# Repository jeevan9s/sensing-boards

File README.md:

# Sensing Boards

A collection of sensor and embedded boards designed in KiCad.

## Boards

### Hall-FX Module

An ESP32-S3-based Hall-effect sensing board built around the TI TMAG5273
magnetic sensor. The design also includes USB-C, battery and power-management
circuitry, status LEDs, pushbuttons, ESD protection, and supply decoupling.
I worked with [Johann Samuel Nana](https://www.linkedin.com/in/johann-s-nana/)
([GitHub](https://github.com/sam93502)) on the schematic capture.

- [KiCad project](hall-fx/HALL_module.kicad_pro)
- [Schematic](hall-fx/HALL_module.kicad_sch)
- [PCB layout](hall-fx/HALL_module.kicad_pcb)
- Custom footprints, symbol, and 3D models are in the [hall-fx directory](hall-fx/).

### ToF Sensor Module

A time-of-flight distance-sensing board using the ST VL53L0CX sensor. Its
schematic provides a 3.3 V supply, I2C connections, and an XSHUT control signal,
with ESD protection and decoupling. Designed for Penguin, the modules are
intended to be chained using their I2C input and output connections.

- [KiCad project](tof-module/TOF_module.kicad_pro)
- [Schematic](tof-module/TOF_module.kicad_sch)
- [PCB layout](tof-module/TOF_module.kicad_pcb)

## Working with the designs

Open each board's `.kicad_pro` file in KiCad to view or edit the project. Check
the corresponding schematic for connector pin assignments and electrical
requirements before connecting a board. The project directories also contain
`.zip` archives of the PCB files.

---
Jeevan Sanchez, 2026

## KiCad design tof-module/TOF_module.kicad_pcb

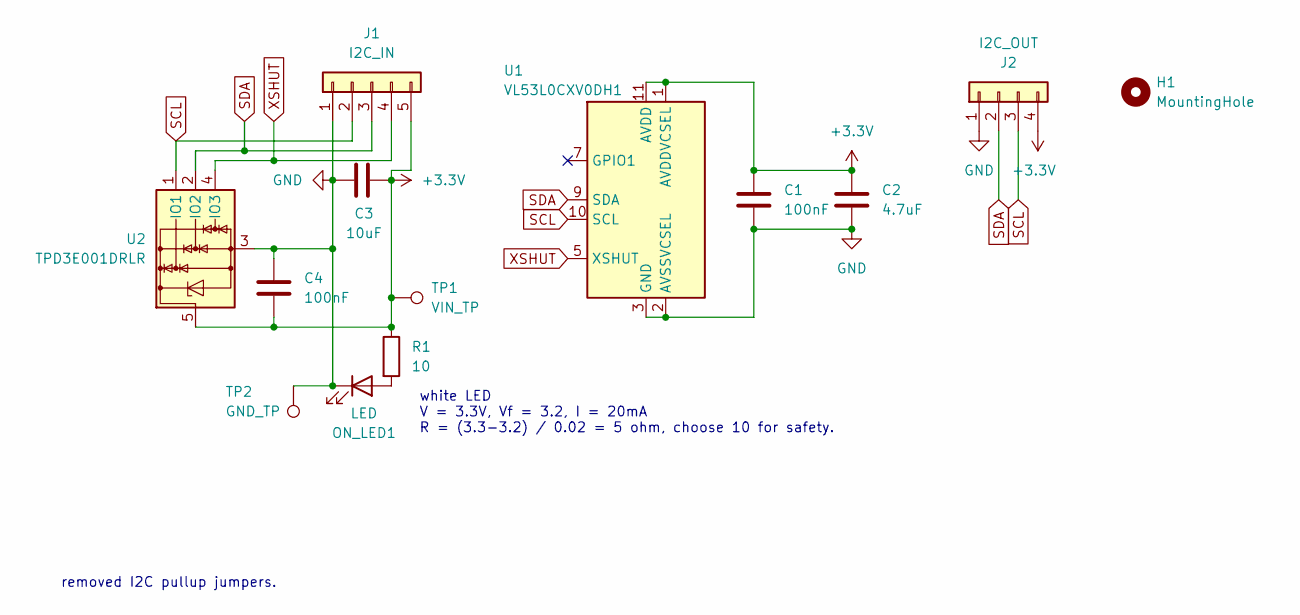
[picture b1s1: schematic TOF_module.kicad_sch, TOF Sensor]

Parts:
C1, C4: 100nF; C_0603_1608Metric
C2: 4.7uF; C_0603_1608Metric
C3: 10uF; C_0805_2012Metric
H1: MountingHole; MountingHole_2.1mm
J1: I2C_IN; JST_GH_BM05B-GHS-TBT_1x05-1MP_P1.25mm_Vertical
J2: I2C_OUT; JST_GH_SM04B-GHS-TB_1x04-1MP_P1.25mm_Horizontal
ON_LED1: LED; LED_0603_1608Metric
R1: 10; R_0603_1608Metric
TP1: VIN_TP; TestPoint_Pad_1.0x1.0mm
TP2: GND_TP; TestPoint_Pad_1.0x1.0mm
U1: VL53L0CXV0DH1; ST_VL53L1x
U2: TPD3E001DRLR; SOT-553

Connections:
+3.3V: C1.1, C2.1, C3.2, C4.1, J1.5, J2.4, R1.1, TP1.1 (1_1), U1.1 (AVDDVCSEL), U1.11 (AVDD), U2.5
GND: C1.2, C2.2, C3.1, C4.2, J1.1, J1.MP, J2.1, J2.MP, ON_LED1.1 (K), TP2.1 (1_1), U1.2 (AVSSVCSEL), U1.3 (GND), U1.4 (GND), U1.6 (GND), U1.12 (GND), U2.3
unnamed: ON_LED1.2 (A), R1.2
SCL: J1.2, J2.3, U1.10 (SCL), U2.1 (IO1)
SDA: J1.3, J2.2, U1.9 (SDA), U2.2 (IO2)
XSHUT: J1.4, U1.5 (XSHUT), U2.4 (IO3)

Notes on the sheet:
removed I2C pullup jumpers.
white LED V = 3.3V, Vf = 3.2, I = 20mA R = (3.3-3.2) / 0.02 = 5 ohm, choose 10 for safety.

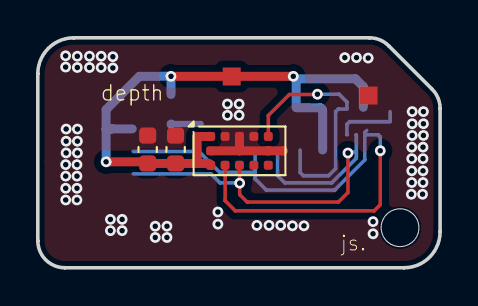
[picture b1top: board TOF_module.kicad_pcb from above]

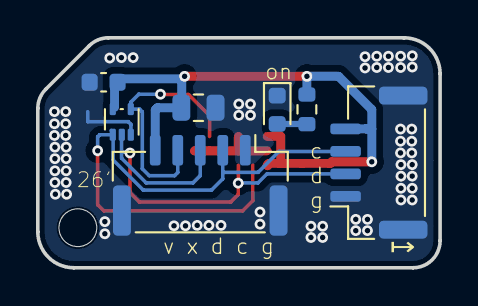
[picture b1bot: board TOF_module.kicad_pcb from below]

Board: 2 copper layers, 22.3 x 12.8 mm, 13 parts (7 on the bottom side), 6 nets.

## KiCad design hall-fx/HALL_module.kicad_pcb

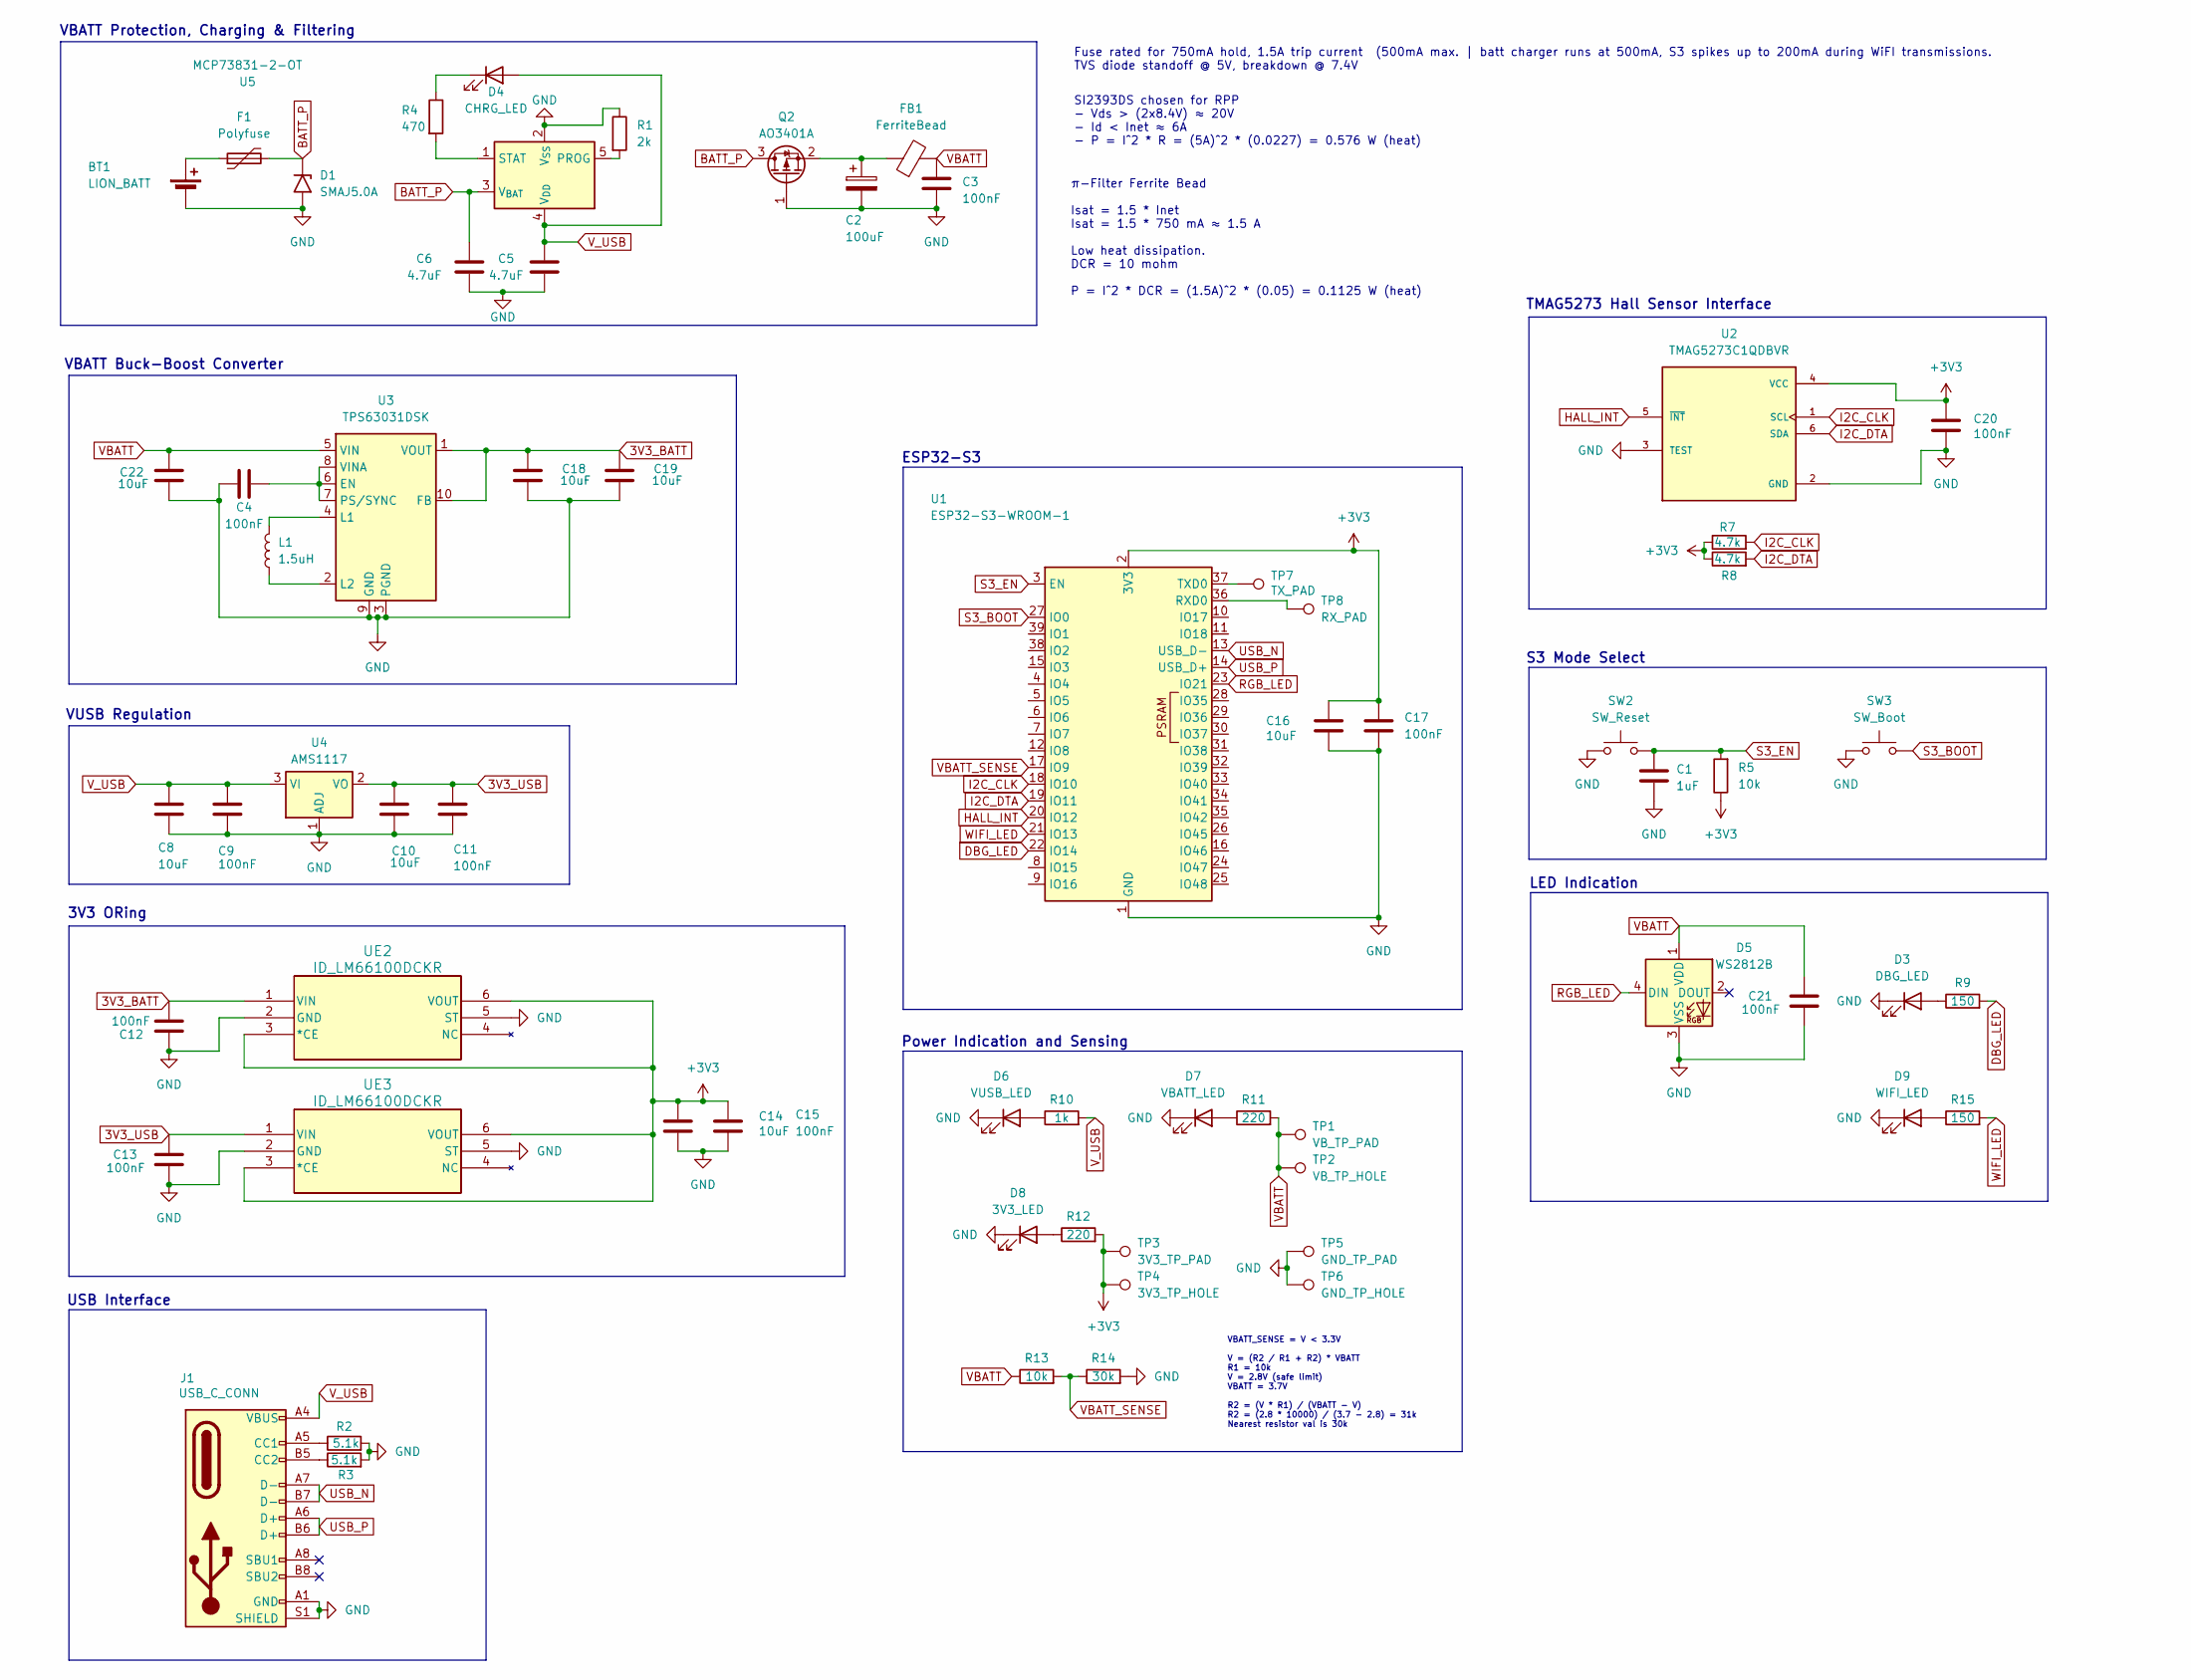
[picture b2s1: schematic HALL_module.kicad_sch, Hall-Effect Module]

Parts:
BT1: LION_BATT; JST_PH_B2B-PH-K_1x02_P2.00mm_Vertical
C1: 1uF; C_0402_1005Metric
C2: 100uF; CP_Elec_6.3x7.7; Digikey 10-EEE-FTH101XALCT-ND
C3: 100nF; C_0603_1608Metric
C4, C9, C11, C12, C13, C15, C17, C20, C21: 100nF; C_0402_1005Metric
C5, C6: 4.7uF; C_0603_1608Metric
C8, C10, C14, C16, C18, C19, C22: 10uF; C_0805_2012Metric
D1: SMAJ5.0A; D_SMF; Digikey SMAJ5.0ALFCT-ND
D3: DBG_LED; LED_0603_1608Metric
D4: CHRG_LED; LED_0603_1608Metric
D5: WS2812B; LED_WS2812B_PLCC4_5.0x5.0mm_P3.2mm
D6: VUSB_LED; LED_0603_1608Metric
D7: VBATT_LED; LED_0603_1608Metric
D8: 3V3_LED; LED_0603_1608Metric
D9: WIFI_LED; LED_0603_1608Metric
F1: Polyfuse; Fuse_1206_3216Metric_Pad1.42x1.75mm_HandSolder; Digikey NANOSMDC075F-2CT-ND
FB1: FerriteBead; R_0805_2012Metric
J1: USB_C_CONN; USB_C_Receptacle_G-Switch_GT-USB-7010ASV; LCSC C5178541
L1: 1.5uH; L_1210_3225Metric_Pad1.42x2.65mm_HandSolder; Digikey 490-5335-1-ND
Q2: AO3401A; SOT-23
R1: 2k; R_0402_1005Metric
R2, R3: 5.1k; R_0402_1005Metric
R4: 470; R_0402_1005Metric
R5, R13: 10k; R_0402_1005Metric
R7, R8: 4.7k; R_0402_1005Metric
R9, R15: 150; R_0402_1005Metric
R10: 1k; R_0402_1005Metric
R11, R12: 220; R_0402_1005Metric
R14: 30k; R_0402_1005Metric
SW2: SW_Reset; SW_5-B-B-B-A_XKB; LCSC C561514
SW3: SW_Boot; SW_5-B-B-B-A_XKB; LCSC C561514
TP1: VB_TP_PAD; TestPoint_Pad_1.0x1.0mm
TP2: VB_TP_HOLE; TestPoint_THTPad_D1.0mm_Drill0.5mm
TP3: 3V3_TP_PAD; TestPoint_Pad_1.0x1.0mm
TP4: 3V3_TP_HOLE; TestPoint_THTPad_D1.0mm_Drill0.5mm
TP5: GND_TP_PAD; TestPoint_Pad_1.0x1.0mm
TP6: GND_TP_HOLE; TestPoint_THTPad_D1.0mm_Drill0.5mm
TP7: TX_PAD; TestPoint_Pad_1.0x1.0mm
TP8: RX_PAD; TestPoint_Pad_1.0x1.0mm
U1: ESP32-S3-WROOM-1
U2: TMAG5273C1QDBVR; SOT95P280X140-6N; PARTREV B
U3: TPS63031DSK; WSON-10-1EP_2.5x2.5mm_P0.5mm_EP1.2x2mm
U4: AMS1117; SOT-223-3_TabPin2
U5: MCP73831-2-OT; SOT-23-5
UE2, UE3: ID_LM66100DCKR; SOT-363_SC-70-6; LCSC C2869734

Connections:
3V3_BATT: C12.1, C18.2, C19.2, U3.1 (VOUT), U3.10 (FB), UE2.1 (VIN)
3V3_USB: C10.2, C11.2, C13.2, U4.2 (VO), UE3.1 (VIN)
+3V3: C14.2, C15.2, C16.2, C17.2, C20.2, R5.1, R7.1, R8.1, R12.2, TP3.1 (1_1), TP4.1 (1_1), U1.2 (3V3), U2.4 (VCC), UE2.3 (*CE), UE2.6 (VOUT), UE3.3 (*CE), UE3.6 (VOUT)
BATT_P: C6.1, D1.1 (A1), F1.2, Q2.3 (D), U5.3 (V_{BAT})
DBG_LED: R9.2, U1.22 (IO14)
GND: BT1.2 (-), C1.1, C2.2, C3.1, C4.1, C5.1, C6.2, C8.1, C9.1, C10.1, C11.1, C12.2, C13.1, C14.1, C15.1, C16.1, C17.1, C18.1, C19.1, C20.1, C21.1, C22.1, D1.2 (A2), D3.1 (K), D5.3 (VSS), D6.1 (K), D7.1 (K), D8.1 (K), D9.1 (K), J1.A1 (GND), J1.A12 (GND), J1.B1 (GND), J1.B12 (GND), J1.S1 (SHIELD), Q2.1 (G), R1.1, R2.2, R3.2, R14.2, SW2.1, SW3.1, TP5.1 (1_1), TP6.1 (1_1), U1.1 (GND), U1.40 (GND), U1.41 (GND), U2.2 (GND), U2.3 (TEST), U3.3 (PGND), U3.9 (GND), U3.11 (PGND), U4.1 (ADJ), U5.2 (V_{SS}), UE2.2 (GND), UE2.5 (ST), UE3.2 (GND), UE3.5 (ST)
HALL_INT: U1.20 (IO12), U2.5 (~INT)
I2C_CLK: R7.2, U1.18 (IO10), U2.1 (SCL)
I2C_DTA: R8.2, U1.19 (IO11), U2.6 (SDA)
unnamed: BT1.1 (+), F1.1
unnamed: D3.2 (A), R9.1
unnamed: D4.1 (K), R4.1
unnamed: D6.2 (A), R10.1
unnamed: D7.2 (A), R11.1
unnamed: D8.2 (A), R12.1
unnamed: D9.2 (A), R15.1
unnamed: J1.A5 (CC1), R2.1
unnamed: J1.B5 (CC2), R3.1
unnamed: C2.1, FB1.1, Q2.2 (S)
unnamed: TP8.1 (1_1), U1.36 (RXD0)
unnamed: TP7.1 (1_1), U1.37 (TXD0)
unnamed: C4.2, U3.6 (EN), U3.7 (PS/SYNC), U3.8 (VINA)
unnamed: L1.2, U3.4 (L1)
unnamed: L1.1, U3.2 (L2)
unnamed: R1.2, U5.5 (PROG)
unnamed: R4.2, U5.1 (STAT)
RGB_LED: D5.4 (DIN), U1.23 (IO21)
S3_BOOT: SW3.2, U1.27 (IO0)
S3_EN: C1.2, R5.2, SW2.2, U1.3 (EN)
USB_N: J1.A7 (D-), J1.B7 (D-), U1.13 (USB_D-)
USB_P: J1.A6 (D+), J1.B6 (D+), U1.14 (USB_D+)
VBATT: C3.2, C21.2, C22.2, D5.1 (VDD), FB1.2, R11.2, R13.1, TP1.1 (1_1), TP2.1 (1_1), U3.5 (VIN)
VBATT_SENSE: R13.2, R14.1, U1.17 (IO9)
V_USB: C5.2, C8.2, C9.2, D4.2 (A), J1.A4 (VBUS), J1.A9 (VBUS), J1.B4 (VBUS), J1.B9 (VBUS), R10.2, U4.3 (VI), U5.4 (V_{DD})
WIFI_LED: R15.2, U1.21 (IO13)

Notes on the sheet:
VBATT Protection, Charging & Filtering
3V3 ORing
USB Interface
VBATT Buck-Boost Converter
SI2393DS chosen for RPP - Vds > (2x8.4V) ≈ 20V - Id < Inet ≈ 6A - P = I^2 * R = (5A)^2 * (0.0227) = 0.576 W (heat)
ESP32-S3
Fuse rated for 750mA hold, 1.5A trip current (500mA max. | batt charger runs at 500mA, S3 spikes up to 200mA during WiFI transmissions. TVS diode standoff @ 5V, breakdown @ 7.4V
S3 Mode Select
VBATT_SENSE = V < 3.3V V = (R2 / R1 + R2) * VBATT R1 = 10k V = 2.8V (safe limit) VBATT = 3.7V R2 = (V * R1) / (VBATT - V) R2 = (2.8 * 10000) / (3.7 - 2.8) = 31k Nearest resistor val is 30k
π-Filter Ferrite Bead Isat = 1.5 * Inet Isat = 1.5 * 750 mA ≈ 1.5 A Low heat dissipation. DCR = 10 mohm P = I^2 * DCR = (1.5A)^2 * (0.05) = 0.1125 W (heat)
LED Indication
VUSB Regulation
Power Indication and Sensing
TMAG5273 Hall Sensor Interface

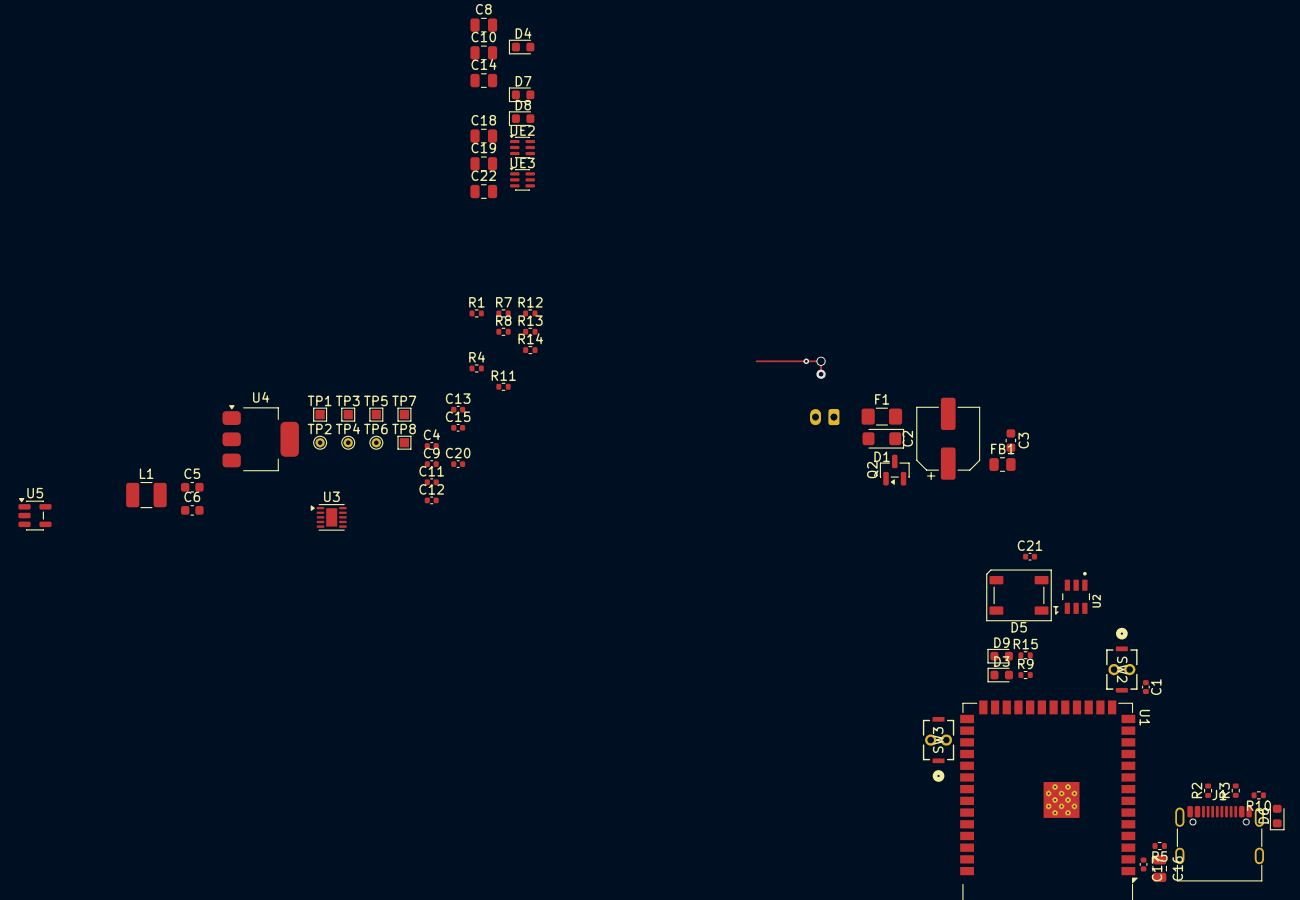
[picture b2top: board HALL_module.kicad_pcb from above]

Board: 2 copper layers, 66 parts (1 on the bottom side), 35 nets.
